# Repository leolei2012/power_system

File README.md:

# power_system

最新方案已收敛为**单功率PWM口**：PWM8P、CTRL、SPI、I²C、ABZ各一路，CAN/TTL/SWD各一路；保留10个独立ADC2P端子和5V输入。按重复功能各减一路的规划，共19个连接器；电机与PFC二选一。推荐沿用已有STM32G431RBT6（LQFP64）物料，44个功能脚已分配、剩8个。见 [当前引脚表](docs/controller_single_power_pin_plan.csv)、[连接器总表](docs/controller_connector_inventory.csv)和 [规划说明](docs/controller_daughterboard.md)。旧双功率口/100脚规划已归档，原生工程仍是Rev E排针版，尚未迁移到端子版。

低压电力电子实验平台。当前 **Rev E为STM32G431RBT6最小系统子板＋应用功率底板**：子板只通过排针插接底板，全部52个可GPIO复用信号pad集中引出；编码器、SPI、TTL、CAN、LED及应用采样/保护均在底板。每套仍控制一路三相桥和一路制动，采用共地、非隔离连接。PFC电源板本阶段暂不绘制。

| 当前工程 | 原理图交付 | PCB 0.1 布局审查 |
| --- | --- | --- |
| [G431最小核](controller/hardware/g431_core/README.md) | 7页、47个位号、3项DNP；[KiCad](controller/hardware/g431_core/controller.kicad_pro)、[PDF](controller/hardware/g431_core/review/controller.pdf) | [60×60mm四层PCB](controller/hardware/g431_core/controller.kicad_pcb) |
| [应用功率底板](inverter/hardware/README.md) | 20页、317个位号、14项DNP；[KiCad](inverter/hardware/inverter.kicad_pro)、[PDF](inverter/hardware/review/inverter.pdf) | [60×60mm六层PCB](inverter/hardware/inverter.kicad_pcb) |

原理图已更新为共享库器件审查稿，双ERC为0错误/0警告；64针、52个信号pad及32768组静态保护/ARM逻辑检查通过。原理图变更、验证与待补物料见 [2026-11-11 原理图交接](docs/schematic_update_2026-11-11.md)。两块PCB已建立60×60mm布局审查稿，上层功率板、下层G431最小核，轮廓边线对齐；四个M2安装孔中心相距52×52mm。实际布线、未连接与DRC状态见 [PCB交接及预览](docs/pcb_review_2026-11-11.md)，板距、插合及散热仍待验证。当前连接和使用方法见 [最小核与功率底板](docs/controller_daughterboard.md)，实际位号见 [子板BOM](controller/hardware/g431_core/bom/bom.csv)和 [底板BOM](inverter/hardware/bom/bom.csv)。

两组2×16、2.54 mm排针共64针：52个MCU信号pad、2针5 V输入、2针核心3.3 V参考、CTRL_READY及7地。子板全部引出，底板9个未用插座脚显式NC。子板独立使用时仍从J101/1、3送入4.75～5.25 V，不增加独立电源/调试连接器；禁止并联两路5 V来源。

子板保留MCU及去耦/VDDA/VREF、可选HSE、RESET/BOOT按钮、本地5 V转3.3 V及监控。PC7在插底板时保留RUN_ARM职责：NRST经U103施密特缓冲后，与默认下拉的PC7通过U105相与生成CTRL_READY。ROM启动和复位阶段不因NRST释放就自动许可功率桥。SWD、BOOT和ROM串口使用条件见 [引脚说明](inverter/docs/pin_assignment.md)。

功率目标沿用12～60 V直流母线、直流输入最大10 A、每相连续10 Arms及20 kHz桥PWM。底板另接12～24 V辅助电源，产生驱动12 V、5 V及本地3.3 V。子板3.3 V总负载预算100 mA，底板回传钳位的短时总正向注入预算50 mA；两侧3.3 V不并联。共地结构不保证炸管后MCU存活，额定、动态保护、插接和热仍待实物验证。

电源板的Boost/Vienna版本及PFC＋LLC仍属后续规划，相关输入、变比和单MCU资源不由本次原理图确认。实验链路与长期讨论见 [架构](vfd/docs/architecture.md)和 [路线图](docs/roadmap.md)；当前先用实验直流源。

## 历史与器件约定

上一版40针、应用接口在子板的Rev D已整体 [归档](inverter/history/daughterboard_rev_d_before_minimum_core_2026-11-07.zip)，不能与Rev E混插。原 [LKS controller](controller/hardware/controller.kicad_sch)仍保留历史；更早的 [Rev C集成板](inverter/history/integrated_rev_c_60x60/)、[Rev A](inverter/history/split_rev_a_2026-11-06.zip)及 [PCB0.1](inverter/history/pcb_0_1_200x140_before_60mm_2026-11-06.zip)不覆盖当前双板。

器件统一在国内立创商城选型，采购链接使用国内商品页；普通小贴片阻容统一YAGEO，分流、电解及稳定性关键电容另行选型。相邻公共库为kicad_library；项目draft符号/封装不等于公共库reviewed或实物验证。两板bom目录分别保留完整型号待定和公共库待建清单，原生图与实际XML为连接依据。参考资料见 [reference](reference/README.md)及 [ATK-PD6010B](reference/ATK-PD6010B/README.md)。

上一轮21款待建型号已全部入库并接入原理图，另复用已reviewed的100nF / 0603电容。目前已选型号无需重复建库，剩余 **65组、233个位号** 待确定完整采购料号，见 [当前待选CSV](docs/parts_to_complete_2026-11-11/selection_pending.csv)与 [交接说明](docs/schematic_update_2026-11-11.md)。[2026-11-10 清单和Excel](docs/parts_to_complete_2026-11-10.md)保留为历史快照。

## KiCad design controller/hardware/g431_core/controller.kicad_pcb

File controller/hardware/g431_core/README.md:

# Rev E STM32G431最小系统板

本工程为 **只通过两组2×16排针连接底板的G431最小核**。七页原理图已完成，47个位号、3项HSE默认DNP；全部52个可GPIO复用信号pad引出。2026-11-11已将20个位号同步为共享库reviewed符号及封装，本轮核心ERC0错误/0警告，233个物理引脚节点与迁移前等价，64针/52pad核对通过；双板系统检查已统一刷新并为PASS。已建立 [controller.kicad_pcb](controller.kicad_pcb)四层PCB 0.1布局审查稿，实际布线/DRC见 [双板PCB交接](../../../docs/pcb_review_2026-11-11.md)。两板均60×60mm，本板位于下层，轮廓边线对齐；四角M2孔心距52×52mm，装配仍待验证。

- [KiCad](controller.kicad_pro)、[原理图](controller.kicad_sch)、[PDF](review/controller.pdf)、[实际XML](review/controller.net.xml)
- [MCU脚表](STM32G431RBT6_pin_plan.csv)、[BOM](bom/bom.csv)、[待选](bom/selection_pending.csv)、[候选入库](bom/library_intake.csv)
- [64针、供电和启动操作](../../../docs/controller_daughterboard.md)、[应用脚表](../../../inverter/docs/pin_assignment.md)、[本地供电分析](core_supply_design.md)
- [本轮迁移记录](review/shared_parts_2026-11-11/migration.json)、[逐pin等价](review/shared_parts_2026-11-11/pin_equivalence.json)、[共享封装引脚检查](review/shared_parts_2026-11-11/footprint_pin_check.json)、[SVG](review/shared_parts_2026-11-11/svg/)

## 最小核范围

仅保留MCU/去耦、VDDA/VREF、RESET/BOOT按钮、可选DNP晶振及负载电容、本地5 V转3.3 V/监控、ARM许可和GPIO排针。SWD/TTL/ABZ/SPI/CAN专用接口、四个GPIO LED及ADC应用滤波/钳位全部在底板，不在最小核重复放置。

64针包含52个MCU信号pad、2针5 V输入、2针核心3.3 V参考、CTRL_READY和7地，子板无GPIO NC。52是可复用物理pad数量，并非52个可同时自由使用GPIO：PG10保留NRST，PF0/PF1与HSE复用，PB8与BOOT0复用，PA13/PA14默认SWD。底板九个未用socket脚NC属于底板用途，不改变最小核引出情况。

U103将NRST缓冲成CORE_RESET_OK，U105再与PC7相与输出CTRL_READY。R402 10k使PC7默认低；插底板时PC7必须保留RUN_ARM职责，应用完成安全初始化后才能主动拉高。独立使用可按GPIO使用PC7。NRST释放不等于功率桥允许运行。

## 供电、调试与BOOT

独立使用从J101/1、3输入 **4.75～5.25 V**，接相应GND；插底板时由底板供电，不增加独立连接器，禁止并联两个5 V源。TLV76733DRVR产生本地+3V3_MCU，总负载预算100 mA。J101/22、32输出核心参考，仅供底板回传钳位/故障上拉及调试电平参考，不能并入底板本地3.3 V或作为其通用电源。

独立板从GPIO排针接PA13/SWDIO、PA14/SWCLK、NRST、3.3 V VTREF和GND；插底板时可用底板SWD口。NRST有本地监控/按键，外部仅作开漏拉低，不用推挽驱动。

物理BOOT法要求选项位 **nSWBOOT0=1、nBOOT1=1、BOOT_LOCK=0**。按住BOOT，按下并释放RESET，再松开BOOT。ROM USART3使用 **PC10_TX/PC11_RX**，不是应用TTL的PB10/PB11；使用时断开复用这两脚的SPI B外设。ROM阶段PC7保持默认低，功率桥不得取得ARM许可。

## 机械与限制

排针为XFCN PZ254V-12-32P / C22465940，配套底板排母PM254V-12-32-H85 / C46595991，两组2×16/P2.54。公头已采用共享库reviewed符号及厂家尺寸封装；子板顶面male朝上、功率板底面female朝下，实际插合、两板布局及装配仍须验证。母座8.5 mm只是塑高，不冻结板距，需按相向元件、插合及通风/装配余量决定。Rev E不兼容上一版40针接口。

MCU放在下层控制板顶面、朝两板之间，避开上板功率热源及高dv/dt铜区投影。RESET（SW2）和BOOT（SW3）均在控制板顶面、与MCU同面，操作面朝上，靠板边从侧面伸入后向下按，并与排针、M2支柱及线束错开。插合后侧向通道须允许按住BOOT的同时操作RESET。两键已同步为XKB Connection [TS-1101-C-W / C318938](https://item.szlcsc.com/300030.html)的共享reviewed符号及封装，电气功能不变；实际操作净空须随板距、支撑及线束共同校核，尚未经机械验证。

底板限流/钳位经核心参考轨回传的短时总正向注入预算50 mA，不是硬限流或持续耐受保证。共地、非隔离结构不保证炸管后MCU存活，PCB、采样时序、供电/保护动态及热仍待验证。旧97件迁移子集脚本及Rev D报告仅属历史，不用于覆盖当前最小核。

## 当前复核与待补物料

本轮采用共享件的20个位号包括MCU、两公头、两键、本地电源/保护的已选器件，以及C304/C306/C307/C308的100nF、50V、X7R、0603国巨C14663。其余26个位号仍缺完整采购型号，其中Y1/C83/C84保持DNP；普通待选阻容的数值、封装及已有约束均保留。BOM由根工程按最新XML统一导出。

在本目录可运行 `python tools/migrate_reviewed_parts_2026_11_11.py --verify` 复核本轮前后逐pin等价。该脚本的`--apply`是一次性增量迁移，不用于重新生成工程。备份见 [迁移前快照](history/rev_e_before_shared_parts_2026-11-11.zip)。双板新系统报告入口为 [根工程检查](../../../outputs/schematic_review_2026-11-11/system_check.json)及 [本地系统报告](review/system_check.json)，已按最终XML复核并为PASS；旧报告不能替代本轮复核。

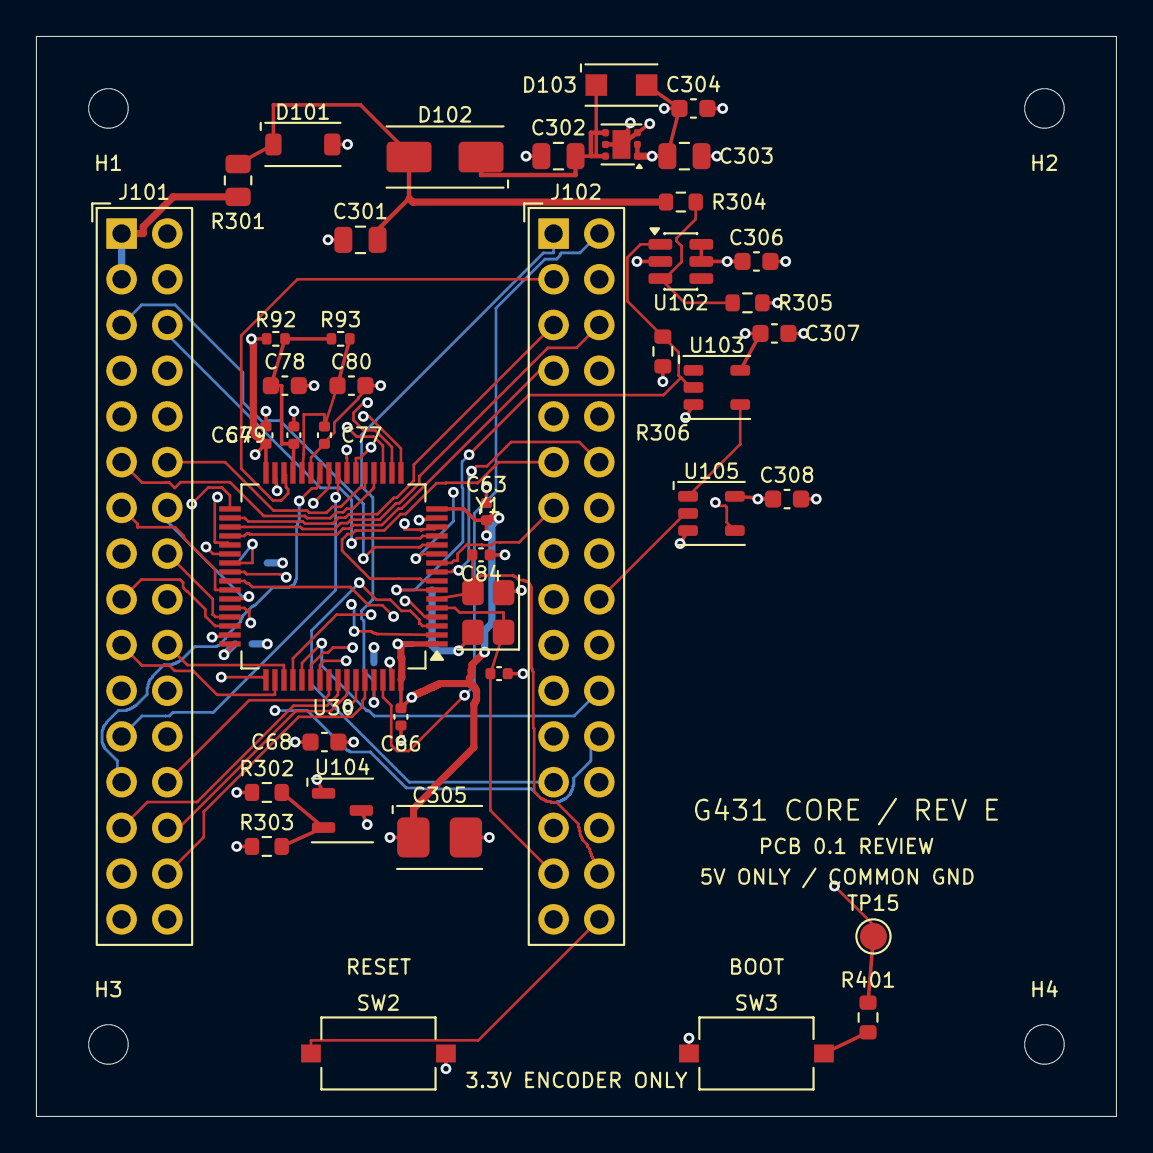
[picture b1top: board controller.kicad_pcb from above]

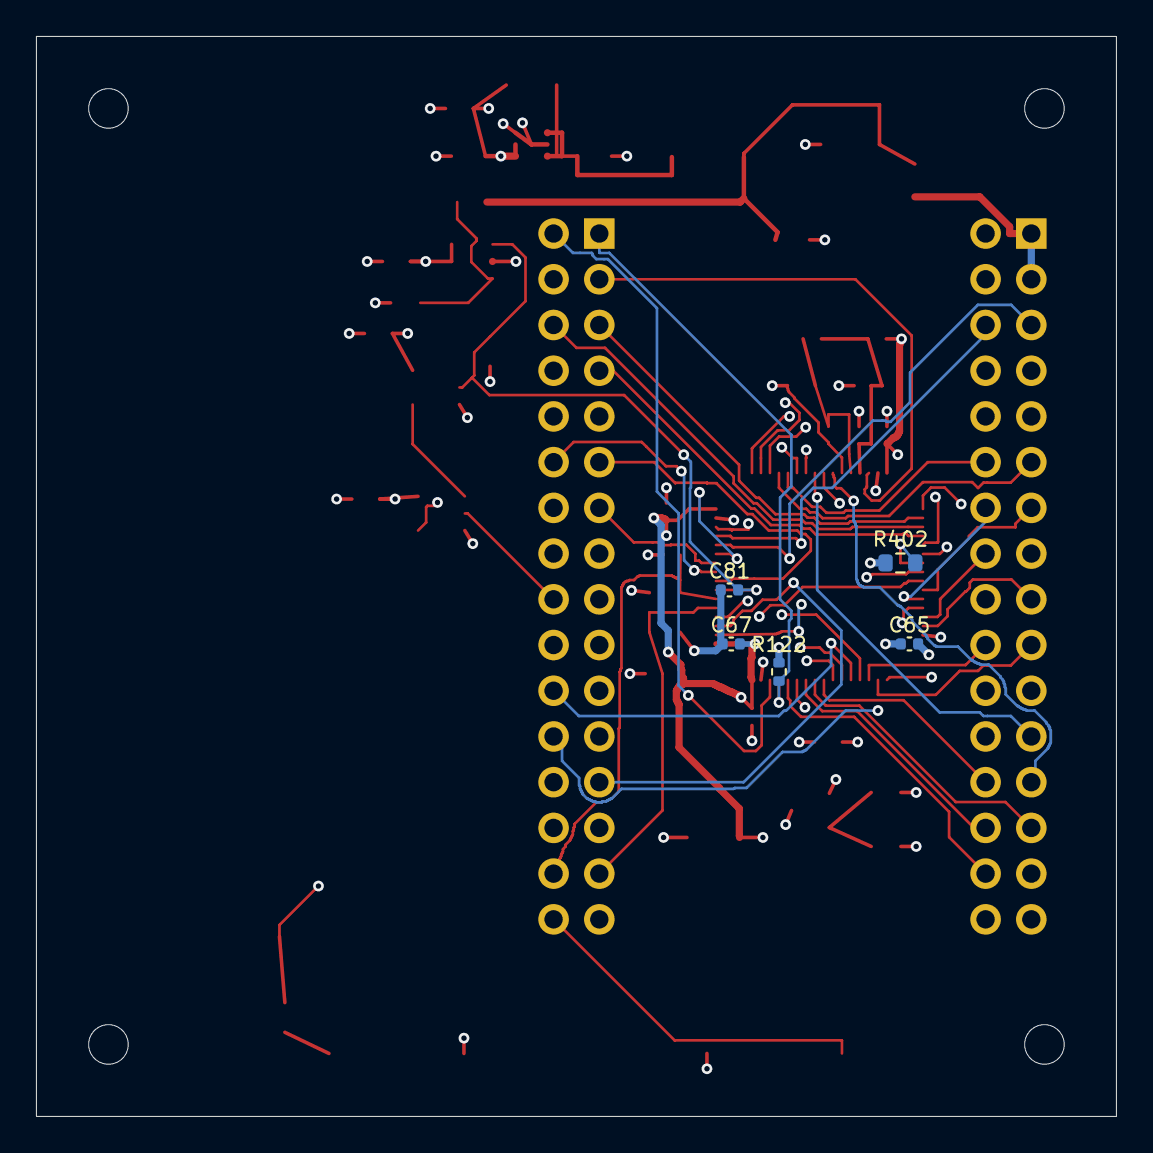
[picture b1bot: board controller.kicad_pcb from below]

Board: 4 copper layers, 60.0 x 60.0 mm, 51 parts (5 on the bottom side), 64 nets.

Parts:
C63, C64, C65, C66, C67, C77, C79, C81: 100n; C_0402_1005Metric
C68: 4.7u; C_0603_1608Metric
C78, C80: 1u; C_0603_1608Metric
C83, C84: 18p / provisional; C_0402_1005Metric
C301, C302, C303: 4.7u; C_0805_2012Metric
C304, C306, C307, C308: 100n; C_0603_1608Metric
C305: 47u 10% 10V; KEMET_T491_B_3528_Pad1.80x2.23mm_Gap1.12mm
D101: SMF6.0A-TP; MCC_SOD-123FL_Pad0.91x1.22mm_Gap2.36mm
D102: S1A-13-F; Diodes_SMA_Pad2.50x1.70mm_P4.00mm
D103: PMEG2010ER,115; Nexperia_CFP3_SOD123W_Reflow
H1, H2, H3, H4: M2 NPTH 2.2mm; MountingHole_2.2mm_M2
J101, J102: PZ254V-12-32P; XFCN_PZ254V-12-32P_2x16_P2.54mm_Vertical_Drill1.02mm
R92, R93: 0; R_0402_1005Metric
R122: 10k; R_0402_1005Metric
R301: 0.47; R_0805_2012Metric
R302: 3.83k 0.1%; R_0603_1608Metric
R303: 10k 0.1%; R_0603_1608Metric
R304, R401: 1k; R_0603_1608Metric
R305: 1.1k; R_0603_1608Metric
R306, R402: 10k; R_0603_1608Metric
SW2: MCU_RESET; XKB_TS-1101-C-W_6.05x3.70mm_Pad1.10x1.00mm
SW3: BOOT; XKB_TS-1101-C-W_6.05x3.70mm_Pad1.10x1.00mm
TP15: BOOT0; TestPoint_Pad_D1.5mm
U30: STM32G431RBT6; ST_LQFP-64_10x10mm_P0.5mm_Pad1.2x0.3mm
U101: TLV76733DRVR; WSON-6-1EP_2x2mm_P0.65mm_EP1x1.6mm
U102: TPS3808G33DBVR; SOT-23-6
U103: SN74LVC1G17DBVR; TI_DBV0005A_Pad1.10x0.60mm_P2.60mm
U104: TL431BIDBZR; TI_DBZ0003A_Pad1.30x0.60mm_P2.10mm
U105: SN74LVC1G08DBVR; TI_DBV0005A_Pad1.10x0.60mm_P2.60mm
Y1: 8MHz / CL TBD / DNP; Crystal_SMD_3225-4Pin_3.2x2.5mm

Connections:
+3V3_A_MCU: C77.1, C78.1, R92.2, R93.1, U30.29
+3V3_MCU: C63.1, C64.1, C65.1, C66.1, C67.1, C68.1, C303.1, C304.1, C305.1, C306.1, C307.1, C308.1, D103.2, J101.22, J101.32, R92.1, R302.1, R306.1, SW3.1, U30.1, U30.16, U30.32, U30.48, U30.64, U101.1, U101.2, U102.5, U102.6, U103.5, U104.1, U105.5
+5V_CORE_IN: J101.1, J101.3, R301.1
/Local power and reset/CORE_5V_TVS: C301.1, D101.1, D102.2, R301.2, R304.1
/Local power and reset/CORE_LDO_IN: C302.1, D102.1, D103.1, U101.4, U101.6
/Local power and reset/CORE_MR_5V_PRESENT: R304.2, R305.1, U102.3
/Local power and reset/CORE_SHUNT_REF: R302.2, R303.1, U104.2
CORE_RESET_OK: U103.4, U105.1
CTRL_READY: J102.10, U105.4
GND: C63.2, C64.2, C65.2, C66.2, C67.2, C68.2, C77.2, C78.2, C79.2, C80.2, C81.2, C83.2, C84.2, C301.2, C302.2, C303.2, C304.2, C305.2, C306.2, C307.2, C308.2, D101.2, J101.2, J101.4, J101.21, J101.31, J102.9, J102.27, J102.31, R122.2, R303.2, R305.2, R402.2, SW2.2, U30.15, U30.27, U30.31, U30.47, U30.63, U101.3, U101.5, U101.7, U102.2, U103.3, U104.3, U105.3, Y1.2, Y1.4
HSE_IN: C83.1, J102.29, U30.5, Y1.1
HSE_OUT: C84.1, J102.30, U30.6, Y1.3
NRST: C81.1, J102.32, R306.2, SW2.1, U30.7, U102.1, U103.2
unnamed: R401.1, SW3.2
PA0: J101.5, U30.12
PA1: J101.6, U30.13
PA2: J101.7, U30.14
PA3: J101.8, U30.17
PA4: J101.9, U30.18
PA5: J101.10, U30.19
PA6: J101.11, U30.20
PA7: J101.12, U30.21
PA8: J101.13, U30.42
PA9: J101.14, U30.43
PA10: J101.15, U30.44
PA11: J101.16, U30.45
PA12: J101.17, U30.46
PA13: J101.18, U30.49
PA14: J101.19, U30.50
PA15: J101.20, U30.51
PB0: J101.23, U30.24
PB1: J101.24, U30.25
PB2: J101.25, U30.26
PB3: J101.26, U30.56
PB4: J101.27, U30.57
PB5: J101.28, U30.58
PB6: J101.29, U30.59
PB7: J101.30, U30.60
PB8_BOOT0: J102.1, R122.1, R401.2, TP15.1, U30.61
PB9: J102.2, U30.62
PB10: J102.3, U30.30
PB11: J102.4, U30.33
PB12: J102.5, U30.34
PB13: J102.6, U30.35
PB14: J102.7, U30.36
PB15: J102.8, U30.37
PC0: J102.11, U30.8
PC1: J102.12, U30.9
PC2: J102.13, U30.10
PC3: J102.14, U30.11
PC4: J102.15, U30.22
PC5: J102.16, U30.23
PC6: J102.17, U30.38
PC7: J102.18, R402.1, U30.39, U105.2
PC8: J102.19, U30.40
PC9: J102.20, U30.41
PC10: J102.21, U30.52
PC11: J102.22, U30.53
PC12: J102.23, U30.54
PC13: J102.24, U30.2
PC14: J102.25, U30.3
PC15: J102.26, U30.4
PD2: J102.28, U30.55
VREF_MCU: C79.1, C80.1, R93.2, U30.28

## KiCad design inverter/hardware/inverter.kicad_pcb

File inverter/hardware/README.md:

# Rev E应用功率底板硬件

2026-11-11已完成当前二十页原理图的共享物料同步，**317个位号、14项DNP**，配套 [七页G431最小核](../../controller/hardware/g431_core/README.md)。底板集中放置功率级与应用电路；本工程ERC0错误/0警告。底板迁移前后的969个物理引脚节点、238条网络分区、64针连接、位号、标称值及DNP均保持等效，见 [本轮核对](review/shared_parts_2026-11-11/pin_equivalence.json)；跨板系统检查见 [system_check.json](review/system_check.json)。

- [KiCad工程](inverter.kicad_pro)、[原理图](inverter.kicad_sch)、[当前PDF](review/inverter.pdf)、[实际XML](review/inverter.net.xml)
- [BOM](bom/bom.csv)、[完整型号待定](bom/selection_pending.csv)、[公共库候选](bom/library_intake.csv)
- [应用脚表](../docs/pin_assignment.md)、[64针定义](../../docs/controller_daughterboard.md)、[设计审查](design_review.md)、[PCB状态](PCB_REVIEW.md)

## 当前电路

功率目标为12～60 V母线、DC输入最大10 A、每相连续10 Arms及20 kHz桥PWM。保留2×220 µF/100 V电解、两只2.2 µF/100 V旁路、三路低端分流/INA241、四路电压及外接NTC前端。Q1～Q7为BSC110N15NS5ATMA1/C412739，D1为MBRD20150CT-13/C151357，现均引用共享MyParts符号与MyFootprints专用封装；连续额定、热和实际装配仍待验证。

比较器、健康链、故障锁存和六路PWM硬件门控均在底板本地。ENABLE与CTRL_READY相与形成运行许可；CTRL_READY来自子板的NRST正常与PC7 RUN_ARM相与。拔板、复位、ROM启动或尚未ARM时保持禁止。FAULT_N由Q8开集电极回传，经1 kΩ/钳位后进入PB12；BASE_READY同样经保护进入PC13。制动仍独立软件控制。

SWD、TTL、两路ABZ、两路SPI、可选经典CAN及五个LED全部在底板。八路ADC的360 Ω/BAT54S钳位和100 Ω/1 nF末端RC也全部在底板，子板只有通用GPIO排针。CAN整支路、传感器5 V连接等按BOM保持DNP；外部信号仍为3.3 V单端。现有TTL口PB10/PB11不是ROM串口入口，ROM使用PC10_TX/PC11_RX，与SPI B复用，见脚表。

辅助入口J2为12～24 V，板上产生12 V驱动、5 V及底板3.3 V。U1 TPS26600的EP17/引脚8是EFUSE_RTN，不是GND；R8仍DNP，SW1接EFUSE_RTN。J101/1、3给子板5 V；J101/22、32接收+3V3_CORE_REF，只供回传保护/故障上拉及SWD VTREF检测，不接底板本地+3V3_INV。

J3/J5为6 mm间距2P焊线孔，J4为15 mm间距U/V/W三孔，现用工程定义为2.0 mm成品孔、4.5 mm铜盘。J5接外置制动电阻，不用可开路；母线不设独立预充或专用放电，输出LC另定。J7传感器供电口默认DNP，J8为外部10k NTC。

## 排针和交付边界

子板使用XFCN PZ254V-12-32P / C22465940，底板使用PM254V-12-32-H85 / C46595991；两组2×16、P2.54。公母器件的共享库定义均已reviewed，底板J101/J102已切换到共享排母符号和1.02 mm钻孔专用封装。规划为下层子板顶面male朝上、上层功率板底面female朝下。母座8.5 mm仅为塑高，实际板距须合并插合几何、两板相向器件高度及通风/装配余量核定；装配面的pin1方向、两板焊盘对位和实物插合仍待PCB/样件验证，不可与旧40针板混插。底板九个未用插座脚NC不影响子板52信号pad全部引出。

两板均 **60×60mm**，上功率板、下G431最小核，同轮廓边线对齐；已建立 [六层inverter.kicad_pcb](inverter.kicad_pcb)及配套四层最小核PCB 0.1布局审查稿，四个2.2mm M2孔心距52×52mm。实际布线/DRC及预览见 [PCB交接](../../docs/pcb_review_2026-11-11.md)，板距、器件干涉和装配仍待验证。新PCB独立于 [Rev C归档](../history/integrated_rev_c_60x60/)；上一版应用子板/底板为 [Rev D历史](../history/daughterboard_rev_d_before_minimum_core_2026-11-07.zip)，旧revd_power.pdf也仅属历史。

上板顶面MOS/电解外露只便于布置。BSC110N15NS5主要由底部焊盘向PCB铜导热，须安排上板背面散热及风道，不能靠交换上下保证10 Arms。下板MCU置于顶面、朝两板之间，避开上板热源及高dv/dt铜区投影。RESET（SW2）/BOOT（SW3）均在下层控制板顶面、与MCU同面，操作面朝上，靠板边从侧面伸入后向下按，并与排针、支柱和线束错开；两键统一采用TS-1101-C-W/C318938，电气功能不变，插合后操作净空须随板距、支撑及线束共同校核。

底板34种确切采购型号、91个位号现均引用已reviewed的共享符号及封装，包括三颗半桥驱动、七颗MOS、D1、钳位二极管、保险、电感、各小排针、SW1及两组排母。17颗100 nF/0603落实为国巨CC0603KRX7R9BB104/C14663，50 V、±10%、X7R，覆盖原25 V局部去耦/自举要求。其余207个位号仍待采购选型（152电阻、50电容、5 LED），未猜填型号；J3/J4/J5焊线孔及测试点不计采购件。SW1仍是辅助电源复位按键TS-1088-AR02016，与子板RESET/BOOT两键独立。

共享器件的reviewed仅说明库定义检查通过，不能作为应用或实物验证。模块内部保留直接连线，独立模块间允许标签。D1改为完整双肖特基符号并重接局部直连线，MOS保留1～3为S、4为G、5～8为D的8物理脚对应。当前共地设计不保证炸管后MCU存活；最终PCB和实物的回流、采样、保护动态、插接及热尚未验证。本轮 [备份清单](review/shared_parts_2026-11-11/backup_manifest.json)、[迁移记录](review/shared_parts_2026-11-11/migration.json)、[PDF](review/shared_parts_2026-11-11/inverter.pdf)、[SVG](review/shared_parts_2026-11-11/svg/)用于追溯。

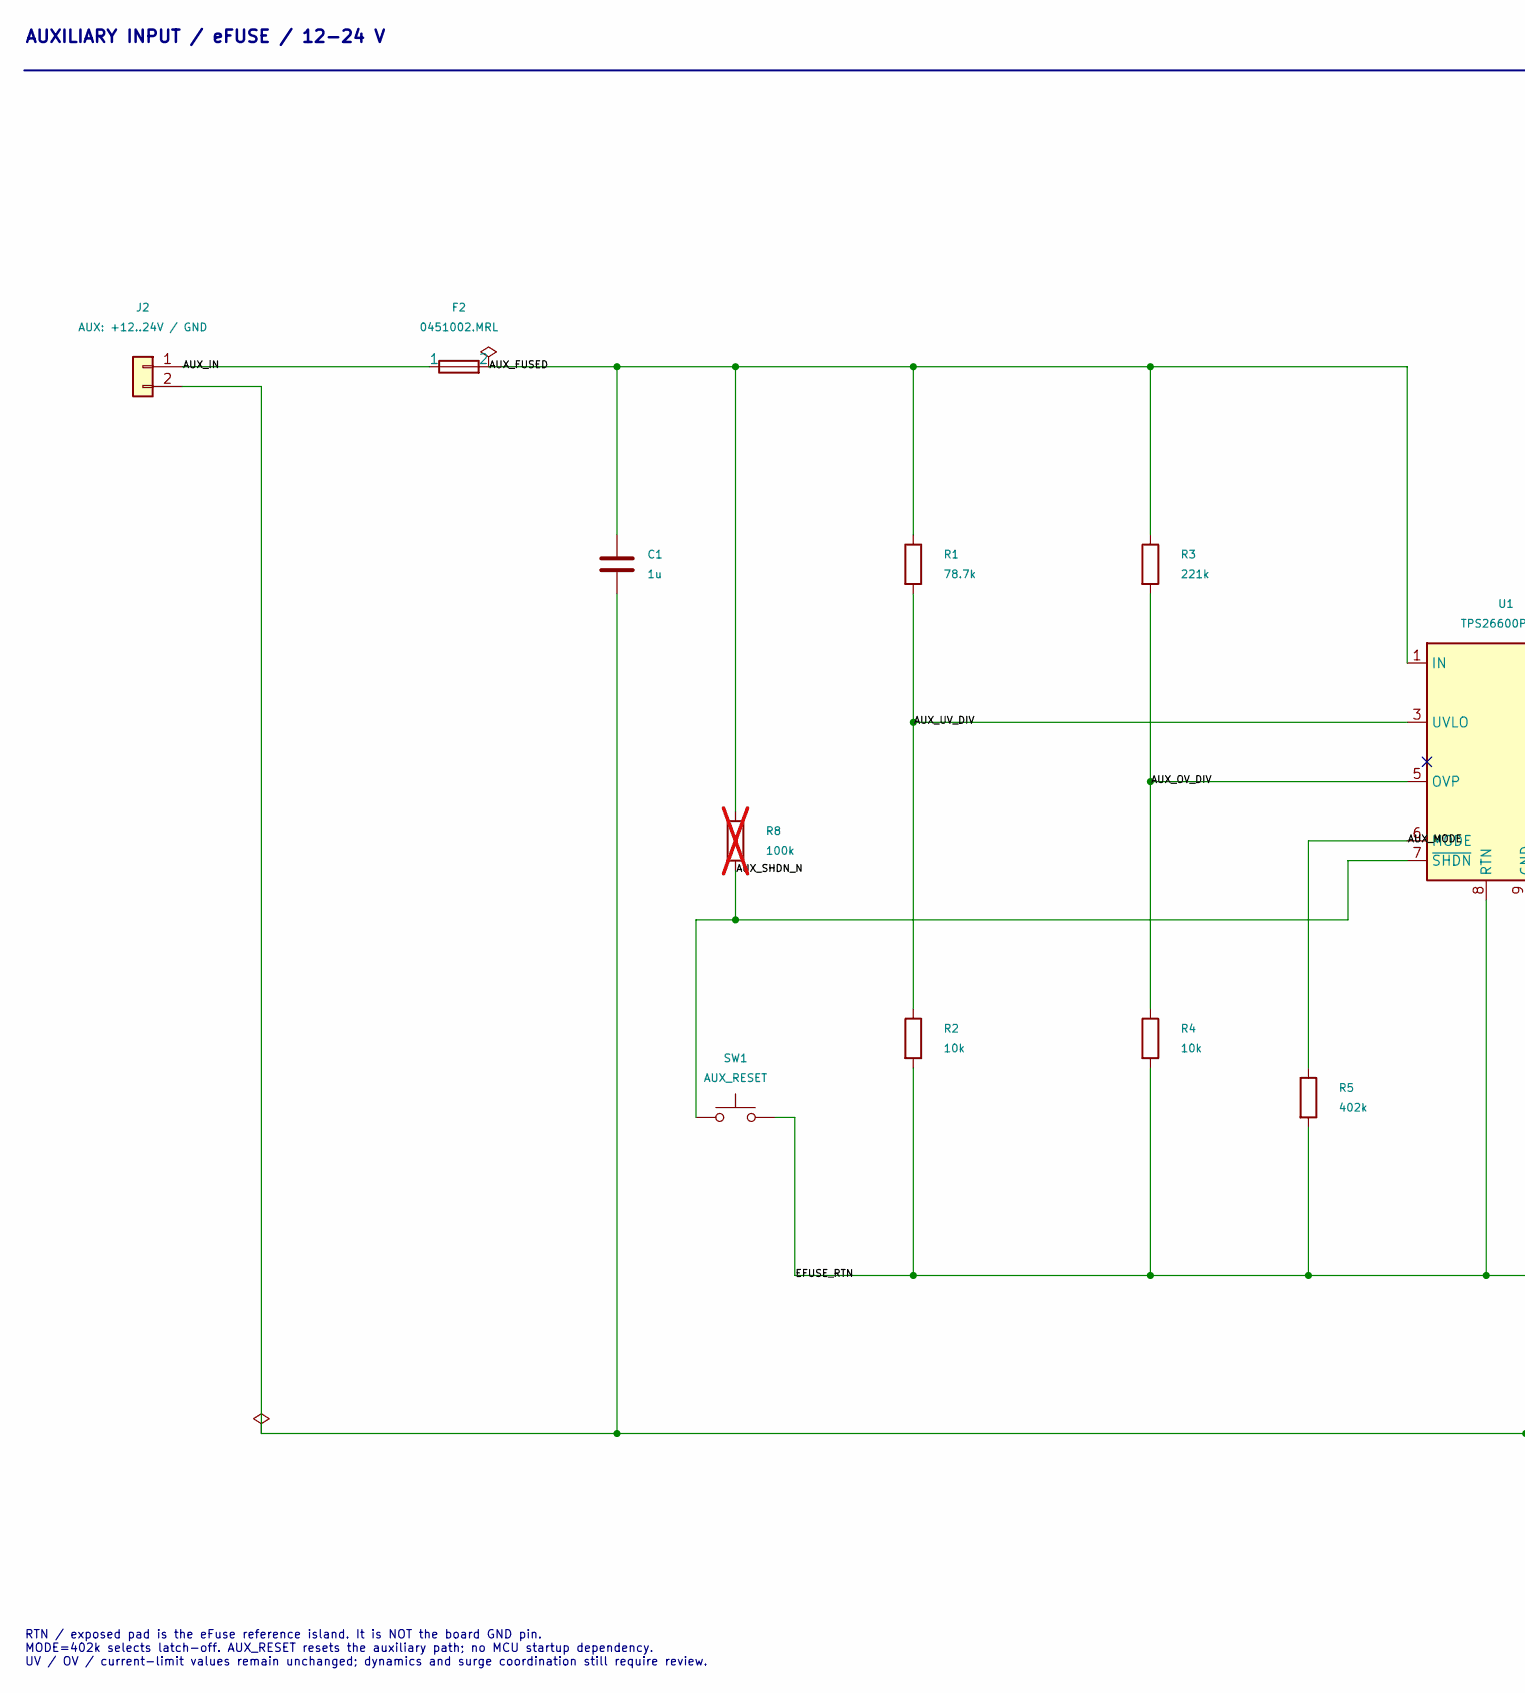
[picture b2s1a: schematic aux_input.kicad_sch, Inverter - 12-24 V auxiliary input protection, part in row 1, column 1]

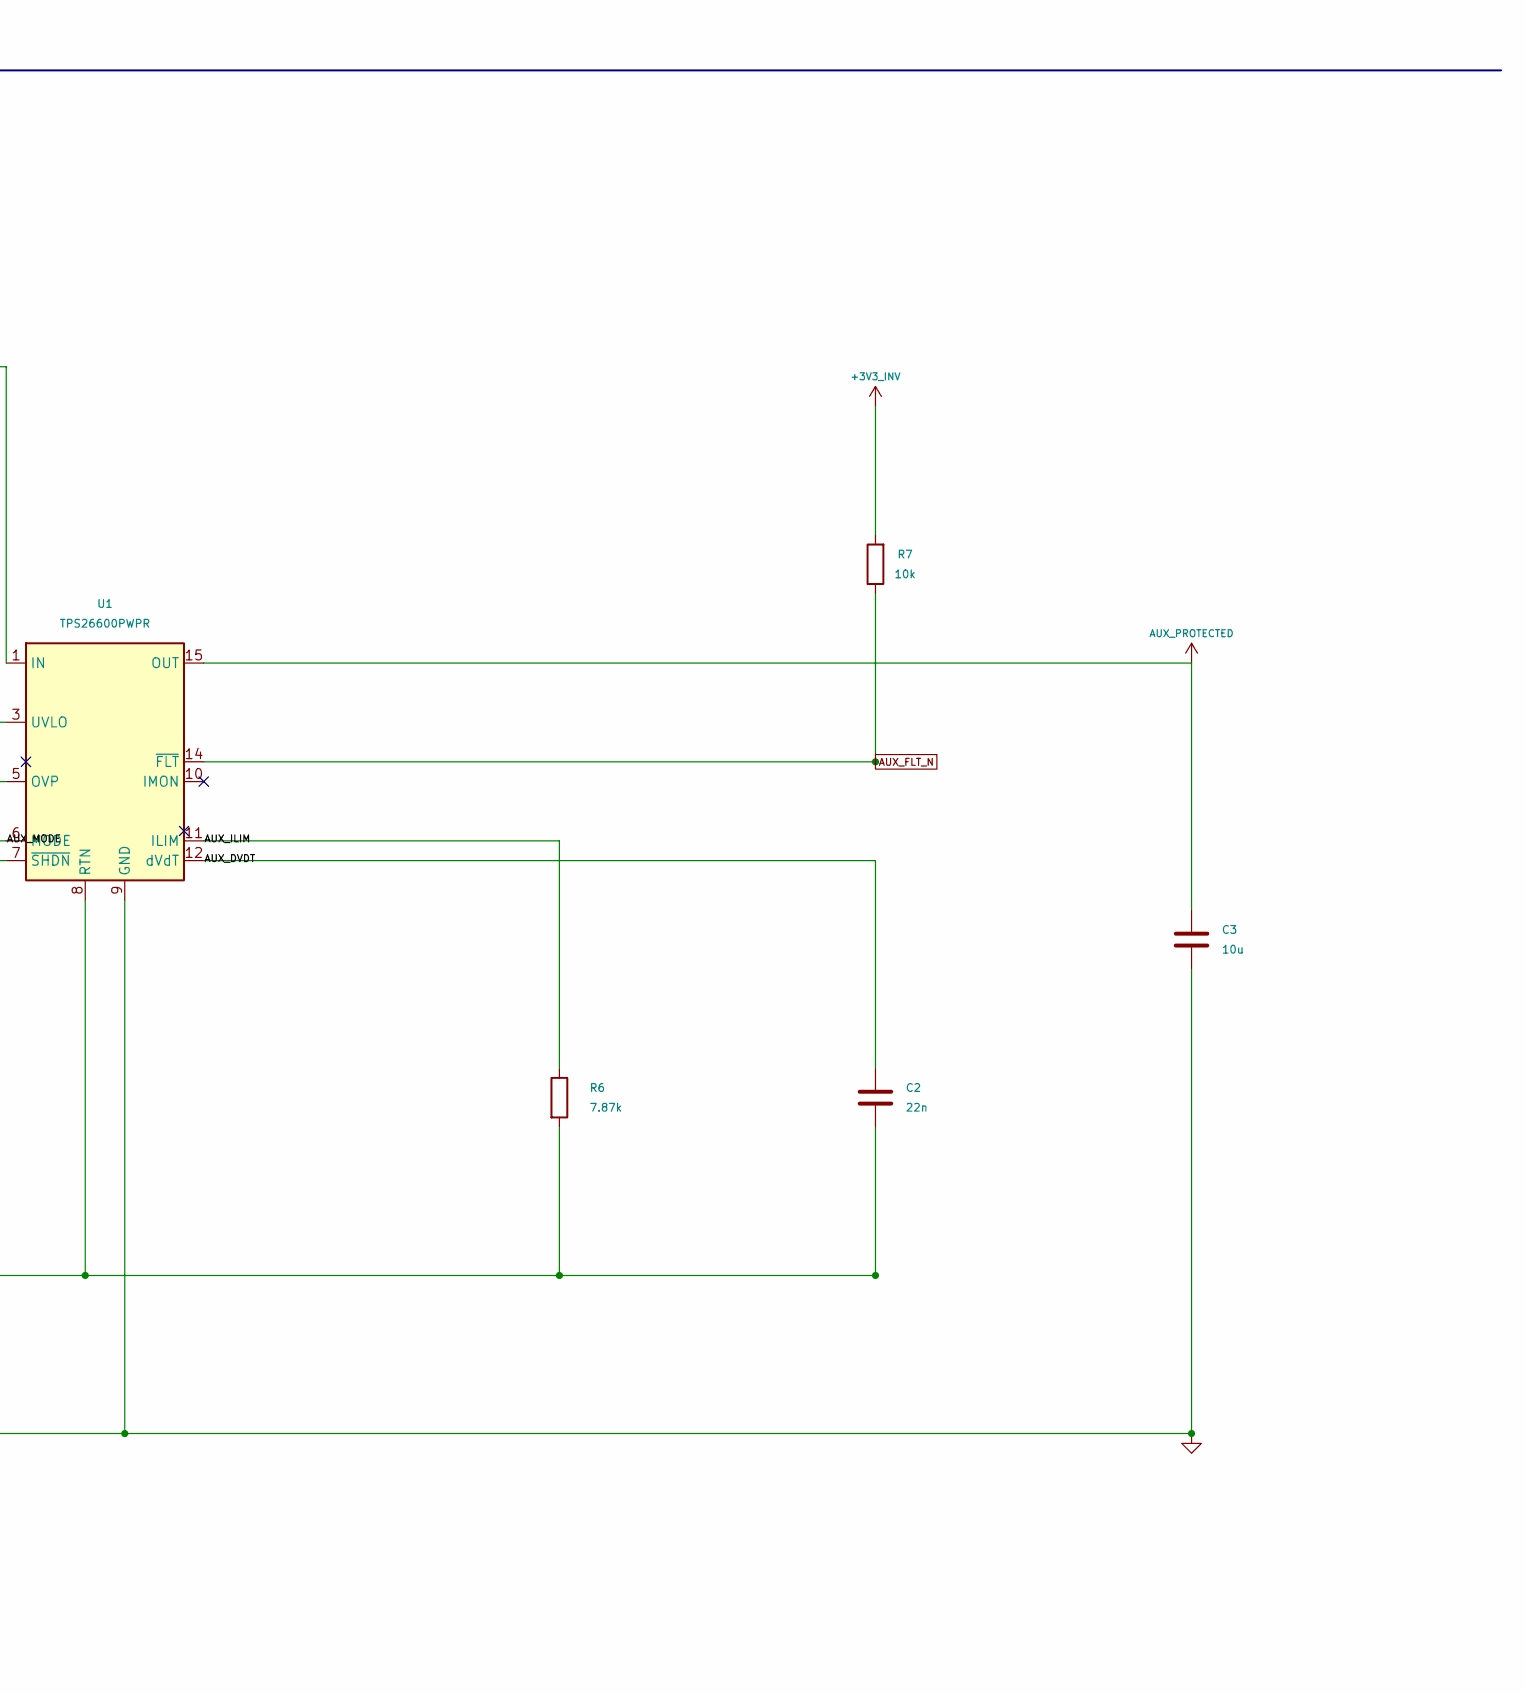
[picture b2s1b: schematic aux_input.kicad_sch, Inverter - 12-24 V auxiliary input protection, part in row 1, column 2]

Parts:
C1: 1u; C_0805_2012Metric; Voltage_Rating 100V; MPN TBD
C2: 22n; C_0603_1608Metric; Voltage_Rating 25V; MPN TBD
C3: 10u; C_1206_3216Metric; Voltage_Rating 50V; MPN TBD
F2: 0451002.MRL; Littelfuse_NANO2_451_476_Pad1.96x3.15mm_Gap2.95mm; MPN 0451002.MRL
J2: AUX: +12..24V / GND; JST_PH_B2B-PH-K_1x02_P2.00mm_Vertical; MPN B2B-PH-K-S(LF)(SN)
R1: 78.7k; R_0603_1608Metric; Tolerance 0.1%; MPN TBD
R2, R4: 10k; R_0603_1608Metric; Tolerance 0.1%; MPN TBD
R3: 221k; R_0603_1608Metric; Tolerance 0.1%; MPN TBD
R5: 402k; R_0603_1608Metric; Tolerance 1%; MPN TBD
R6: 7.87k; R_0603_1608Metric; Tolerance 1%; MPN TBD
R7: 10k; R_0603_1608Metric; Tolerance 1%; MPN TBD
R8: 100k; R_0603_1608Metric; Tolerance 1%; MPN TBD; not fitted
SW1: AUX_RESET; SW_SPST_TS-1088-xR020; MPN TS-1088-AR02016
U1: TPS26600PWPR; HTSSOP-16-1EP_4.4x5mm_P0.65mm_EP3.4x5mm_Mask2.66x2.46mm; MPN TPS26600PWPR

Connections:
+3V3_INV: R7.2; also elsewhere on the board
/Auxiliary input/AUX_DVDT: C2.1, U1.12 (dVdT)
/Auxiliary input/AUX_FUSED: C1.1, F2.2, R1.1, R3.1, R8.1, U1.1 (IN), U1.2 (IN)
/Auxiliary input/AUX_ILIM: R6.1, U1.11 (ILIM)
/Auxiliary input/AUX_IN: F2.1, J2.1
/Auxiliary input/AUX_MODE: R5.1, U1.6 (MODE)
/Auxiliary input/AUX_OV_DIV: R3.2, R4.1, U1.5 (OVP)
/Auxiliary input/AUX_SHDN_N: R8.2, SW1.1, U1.7 (~SHDN)
/Auxiliary input/AUX_UV_DIV: R1.2, R2.1, U1.3 (UVLO)
/Auxiliary input/EFUSE_RTN: C2.2, R2.2, R4.2, R5.2, R6.2, SW1.2, U1.8 (RTN), U1.17 (RTN)
AUX_FLT_N: R7.1, U1.14 (~FLT); also elsewhere on the board
AUX_PROTECTED: C3.1, U1.15 (OUT), U1.16 (OUT); also elsewhere on the board

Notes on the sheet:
AUXILIARY INPUT / eFUSE / 12-24 V
RTN / exposed pad is the eFuse reference island. It is NOT the board GND pin. MODE=402k selects latch-off. AUX_RESET resets the auxiliary path; no MCU startup dependency. UV / OV / current-limit values remain unchanged; dynamics and surge coordination still require review.

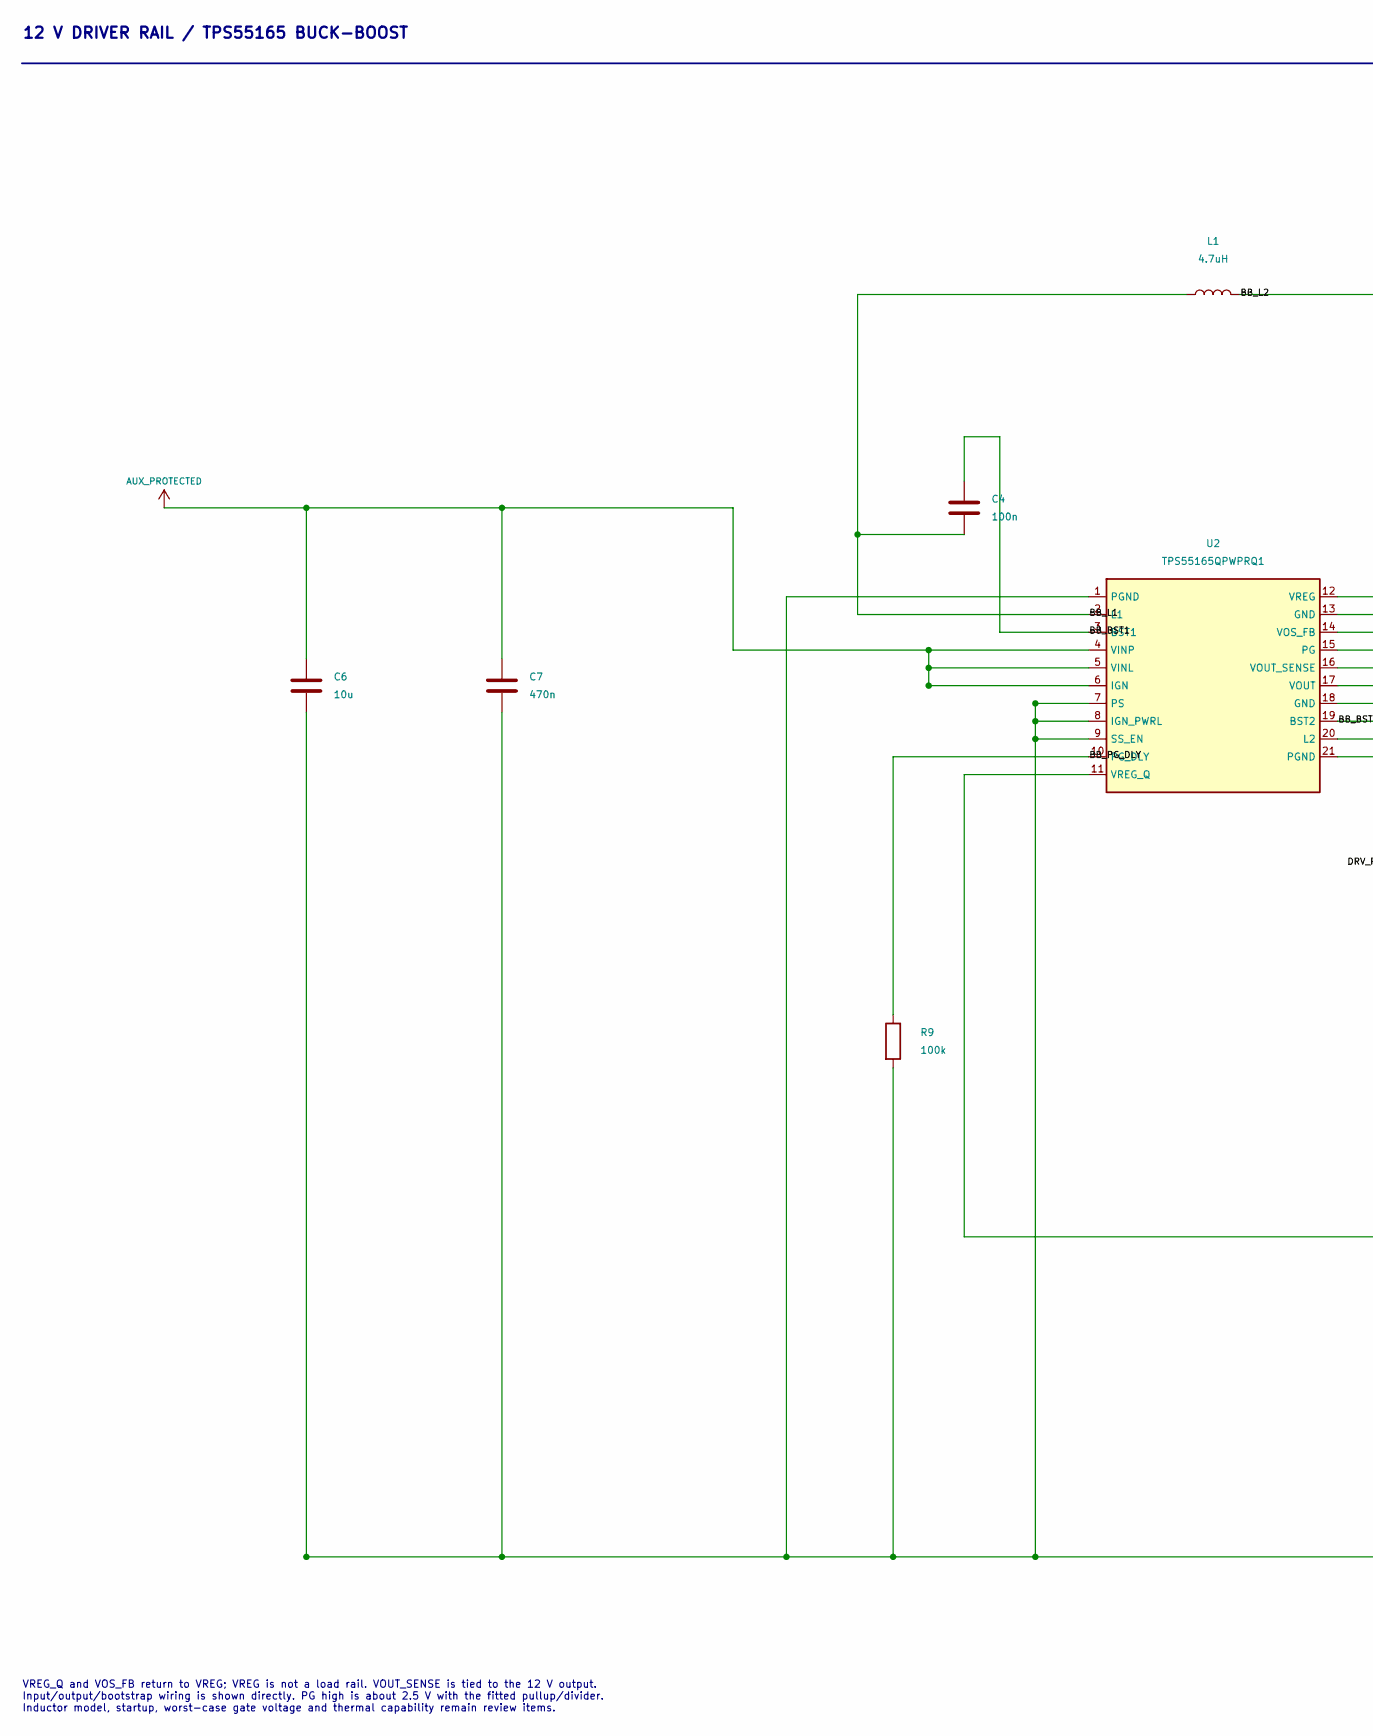
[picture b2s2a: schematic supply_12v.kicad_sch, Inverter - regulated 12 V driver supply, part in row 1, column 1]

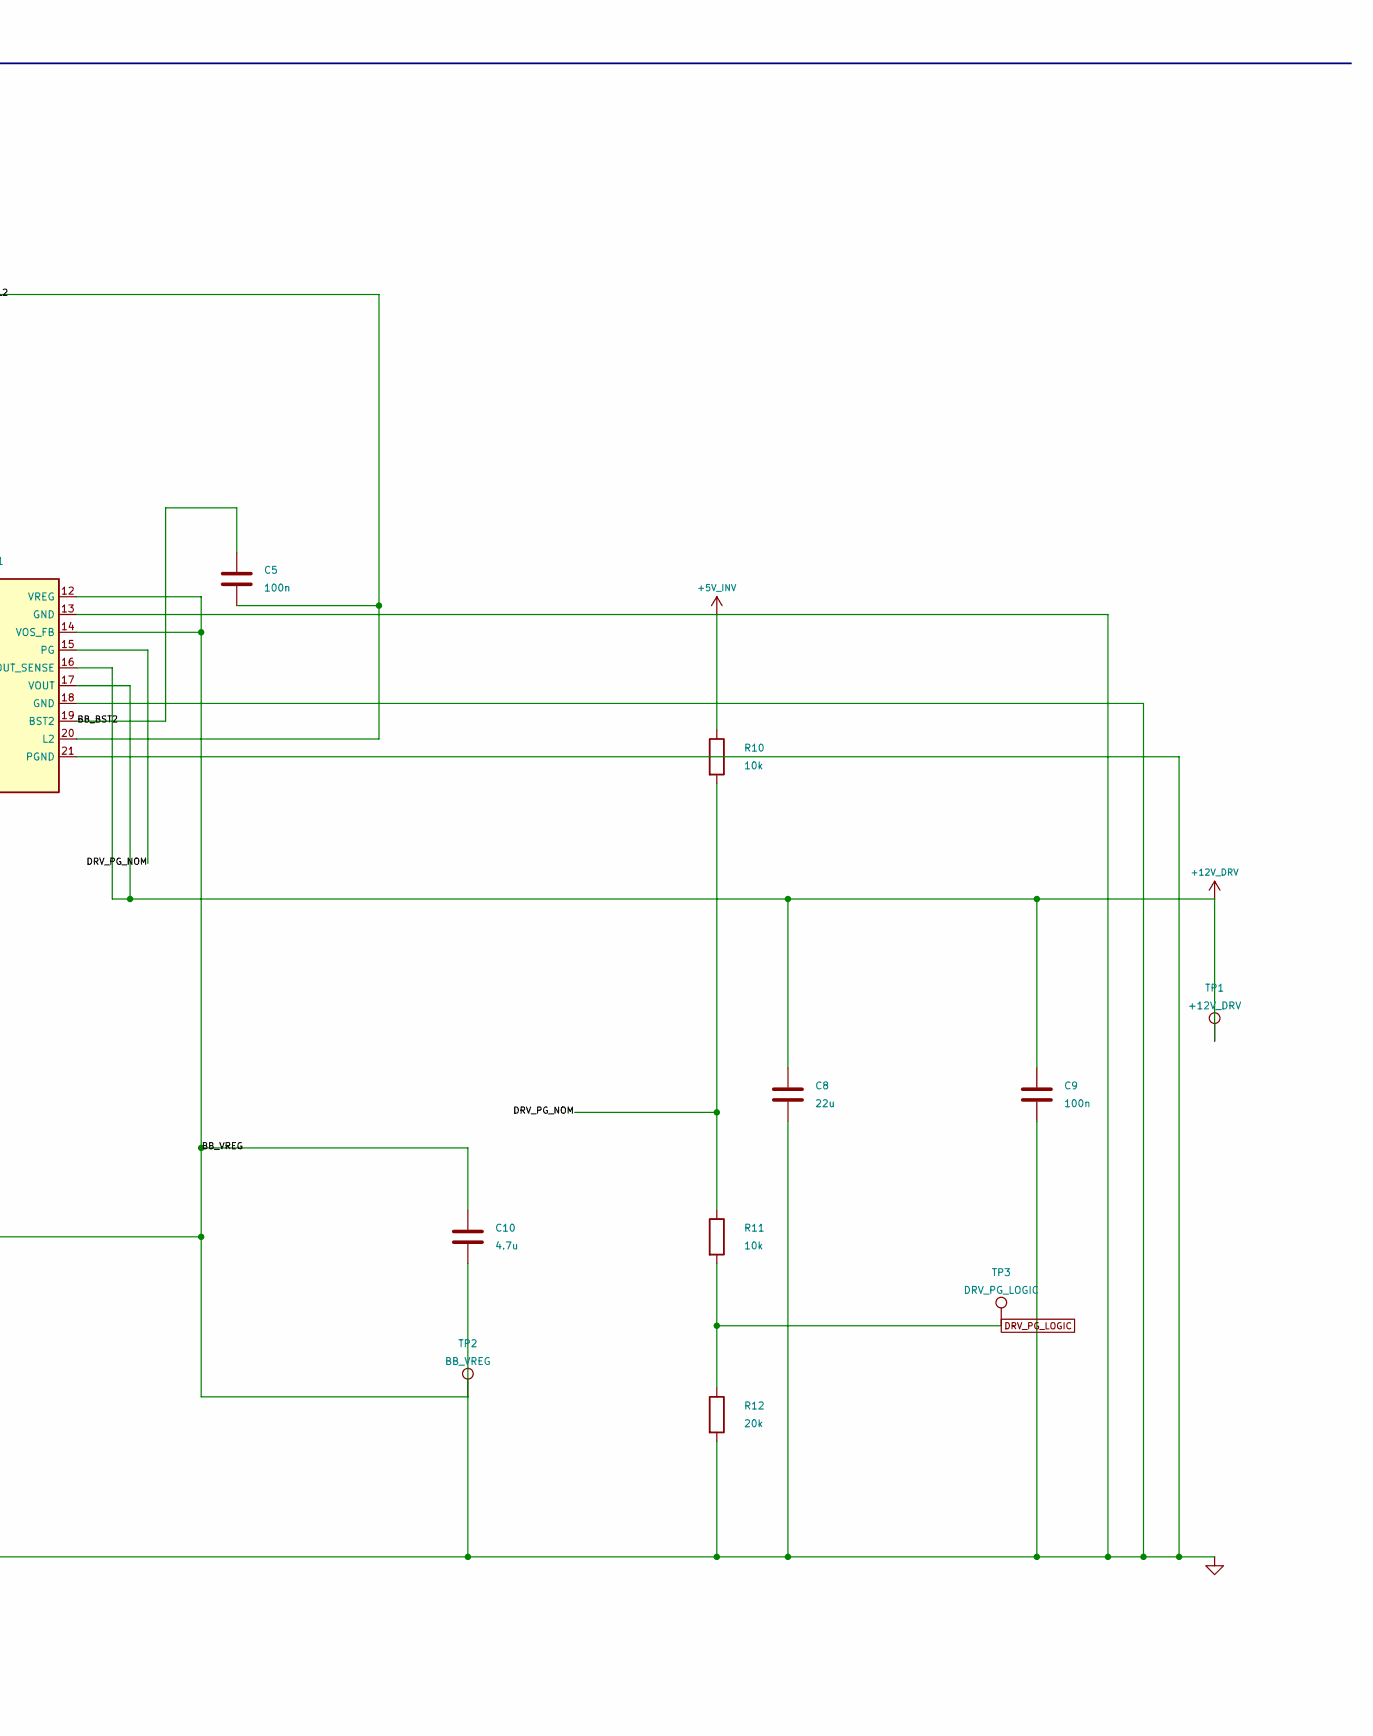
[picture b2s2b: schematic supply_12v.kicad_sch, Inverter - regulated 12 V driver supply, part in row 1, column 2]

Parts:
C4, C5, C9: 100n; C_0603_1608Metric; Voltage_Rating 50V; Tolerance 10%; MPN CC0603KRX7R9BB104
C6: 10u; C_1206_3216Metric; Voltage_Rating 50V; MPN TBD
C7: 470n; C_0805_2012Metric; Voltage_Rating 50V; MPN TBD
C8: 22u; C_1210_3225Metric; Voltage_Rating 25V; MPN TBD
C10: 4.7u; C_0805_2012Metric; Voltage_Rating 10V; MPN TBD
L1: 4.7uH; L_Sunlord_MWSA0603S; MPN MWSA0603S-4R7MT
R9: 100k; R_0603_1608Metric; Tolerance 1%; MPN TBD
R10, R11: 10k; R_0603_1608Metric; Tolerance 1%; MPN TBD
R12: 20k; R_0603_1608Metric; Tolerance 1%; MPN TBD
TP1: +12V_DRV; TestPoint_Pad_D1.5mm
TP2: BB_VREG; TestPoint_Pad_D1.5mm
TP3: DRV_PG_LOGIC; TestPoint_Pad_D1.5mm
U2: TPS55165QPWPRQ1; TI_PWP0020W_HTSSOP-20_4.4x6.5mm_P0.65mm_EP2.79x3.64mm; MPN TPS55165QPWPRQ1

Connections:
+12V_DRV: C8.1, C9.1, TP1.1, U2.16 (VOUT_SENSE), U2.17 (VOUT); also elsewhere on the board
/Driver supply/BB_BST1: C4.1, U2.3 (BST1)
/Driver supply/BB_BST2: C5.1, U2.19 (BST2)
/Driver supply/BB_L1: C4.2, L1.1, U2.2 (L1)
/Driver supply/BB_L2: C5.2, L1.2, U2.20 (L2)
/Driver supply/BB_PG_DLY: R9.1, U2.10 (PG_DLY)
/Driver supply/BB_VREG: C10.1, TP2.1, U2.11 (VREG_Q), U2.12 (VREG), U2.14 (VOS_FB)
/Driver supply/DRV_PG_NOM: R10.2, R11.1, U2.15 (PG)
AUX_PROTECTED: C6.1, C7.1, U2.4 (VINP), U2.5 (VINL), U2.6 (IGN); also elsewhere on the board
DRV_PG_LOGIC: R11.2, R12.1, TP3.1; also elsewhere on the board

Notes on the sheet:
12 V DRIVER RAIL / TPS55165 BUCK-BOOST
VREG_Q and VOS_FB return to VREG; VREG is not a load rail. VOUT_SENSE is tied to the 12 V output. Input/output/bootstrap wiring is shown directly. PG high is about 2.5 V with the fitted pullup/divider. Inductor model, startup, worst-case gate voltage and thermal capability remain review items.
